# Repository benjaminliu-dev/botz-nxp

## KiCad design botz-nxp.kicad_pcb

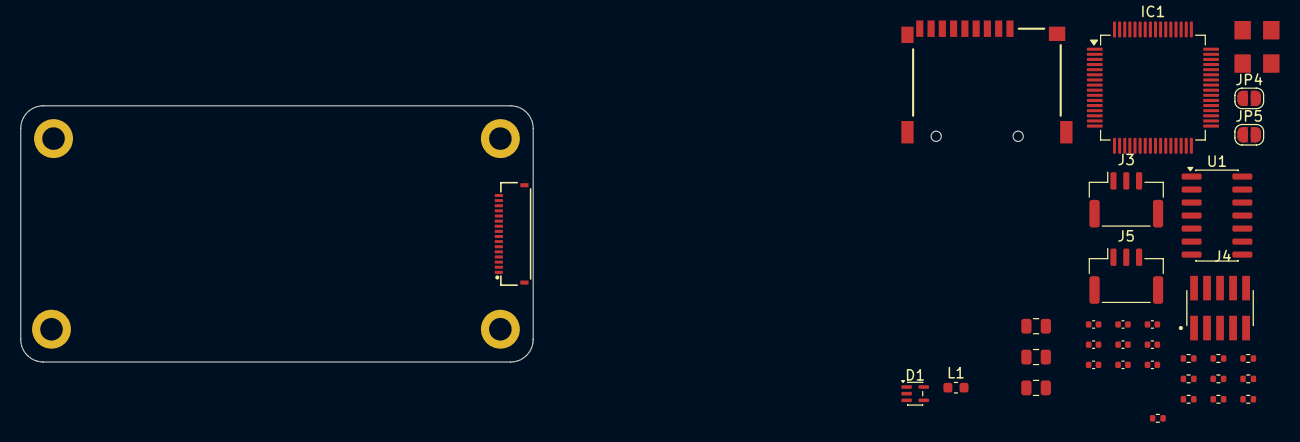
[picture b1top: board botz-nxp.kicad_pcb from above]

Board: 2 copper layers, 50.0 x 25.0 mm, 35 parts (0 on the bottom side), 31 nets, no tracks yet.

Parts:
C1, C2, C3, C4, C8, C9, C13, C15: 0.1uF; C_0402_1005Metric
C5, C6, C14: 10uF; C_0805_2012Metric
C7: 10uF; C_0402_1005Metric
D1: PESD5V0L4UG; SOT-353_SC-70-5
F1: 6V/0.75A/1.5A; 1206
F2: 6V/0.5A/1A; 1206
IC1: MCXA265VLH; LQFP-64_10x10mm_P0.5mm
J1: microSD; microSD_External_Pin
J3, J5: JST_1GH_3; JST_GH_SM03B-GHS-TB_1x03-1MP_P1.25mm_Horizontal
J4: Conn_ARM_JTAG_SWD_10; AMPHENOL_20021121-00010C1LF
J6: Conn_01x16_FPC_0.5mm; FPC_1x16_P0.5mm_Horizontal_DualContact
JP4, JP5: Jumper_2_Open; SolderJumper-2_P1.3mm_Open_RoundedPad1.0x1.5mm
L1: 120 Ohm; L_0603_1608Metric
R1, R3, R4, R5, R6, R7, R8, R10: 10k; R_0402_1005Metric
R2, R9: 120; R_0402_1005Metric
U1: TJA1448AT/0Z; SOIC-14_3.9x8.7mm_P1.27mm

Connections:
3.3V: C1.1, C2.1, C3.1, C4.1, C5.1, C9.2, C14.1, C15.1, D1.3 (K2), F2.2, IC1.13 (VDD_1), IC1.29 (VDD_2), IC1.48 (VDD_3), IC1.60 (VDD_4), J1.4 (VDD), J4.1 (VTref), L1.1, R1.2, R3.2, R4.2, R5.2, R6.2, R7.2, R8.2, U1.11 (VIO)
5V: C7.1, D1.1 (K1), F1.1, U1.3 (VCC)
/3.3V_IN: F2.1, J6.3
/5V_IN: F1.2, J6.1
/BOOT: IC1.53 (P0_6), J6.13, R3.1
/CAN0_H: J3.1, J6.6, R2.2, U1.13 (CANH1)
/CAN0_L: J3.2, J6.7, JP4.1 (A), U1.12 (CANL1)
/CAN0_RX: IC1.59 (P1_3), U1.4 (RXD1)
/CAN0_TX: IC1.58 (P1_2), U1.1 (TXD1)
/CAN1_H: J5.1, J6.10, R9.2, U1.10 (CANH2)
/CAN1_L: J5.2, J6.11, JP5.1 (A), U1.9 (CANL2)
/CAN1_RX: IC1.56 (P1_0), U1.7 (RXD2)
/CAN1_TX: IC1.57 (P1_1), U1.6 (TXD2)
/J_RX: D1.5 (K4), IC1.3 (P1_9), J6.5
/J_TX: D1.4 (K3), IC1.2 (P1_8), J6.4
/NRST: C13.2, IC1.8 (P1_29), J4.10 (~RESET), J6.14, R1.1
/SD_CS: IC1.39 (P3_11), J1.2 (DAT3/CD), R4.1
/SD_DAT1: J1.8 (DAT1), R6.1
/SD_DAT2: J1.1 (DAT2), R7.1
/SD_DET: IC1.16 (P2_2), J1.9 (~DET), R8.1
/SD_MISO: IC1.41 (P3_9), J1.7 (DAT0/SDO), R5.1
/SD_MOSI: IC1.42 (P3_8), J1.3 (CMD/SDI)
/SD_SCK: IC1.40 (P3_10), J1.5 (CLK/SCK)
/SWCLK: IC1.50 (P0_1), J4.4 (SWCLK/TCK)
/SWDIO: IC1.49 (P0_0), J4.2 (SWDIO/TMS)
/SWO: IC1.51 (P0_2), J4.6 (SWO/TDO)
/VDDA: C6.1, C8.1, IC1.12 (VREFH/VDD_ANA), L1.2
GND: C1.2, C2.2, C3.2, C4.2, C5.2, C6.2, C7.2, C8.2, C9.1, C13.1, C14.2, C15.2, D1.2 (A), IC1.11 (VSS/VREFL), IC1.28 (VSS_1), IC1.47 (VSS_2), IC1.61 (VSS_3), J1.6 (VSS), J1.10 (SHIELD), J3.3, J4.3 (GND), J4.5 (GND), J4.9 (GNDDetect), J5.3, J6.2, J6.8, J6.9, J6.12, R10.1, U1.2 (GND), U1.5 (GND), U1.8 (STB2), U1.14 (STB1)
unnamed: IC1.25 (VDD_USB), R10.2
unnamed: JP4.2 (B), R2.1
unnamed: JP5.2 (B), R9.1

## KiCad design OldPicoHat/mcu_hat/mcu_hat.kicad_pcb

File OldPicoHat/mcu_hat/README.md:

Raspberry Pi Pico HAT, made by Arnav G

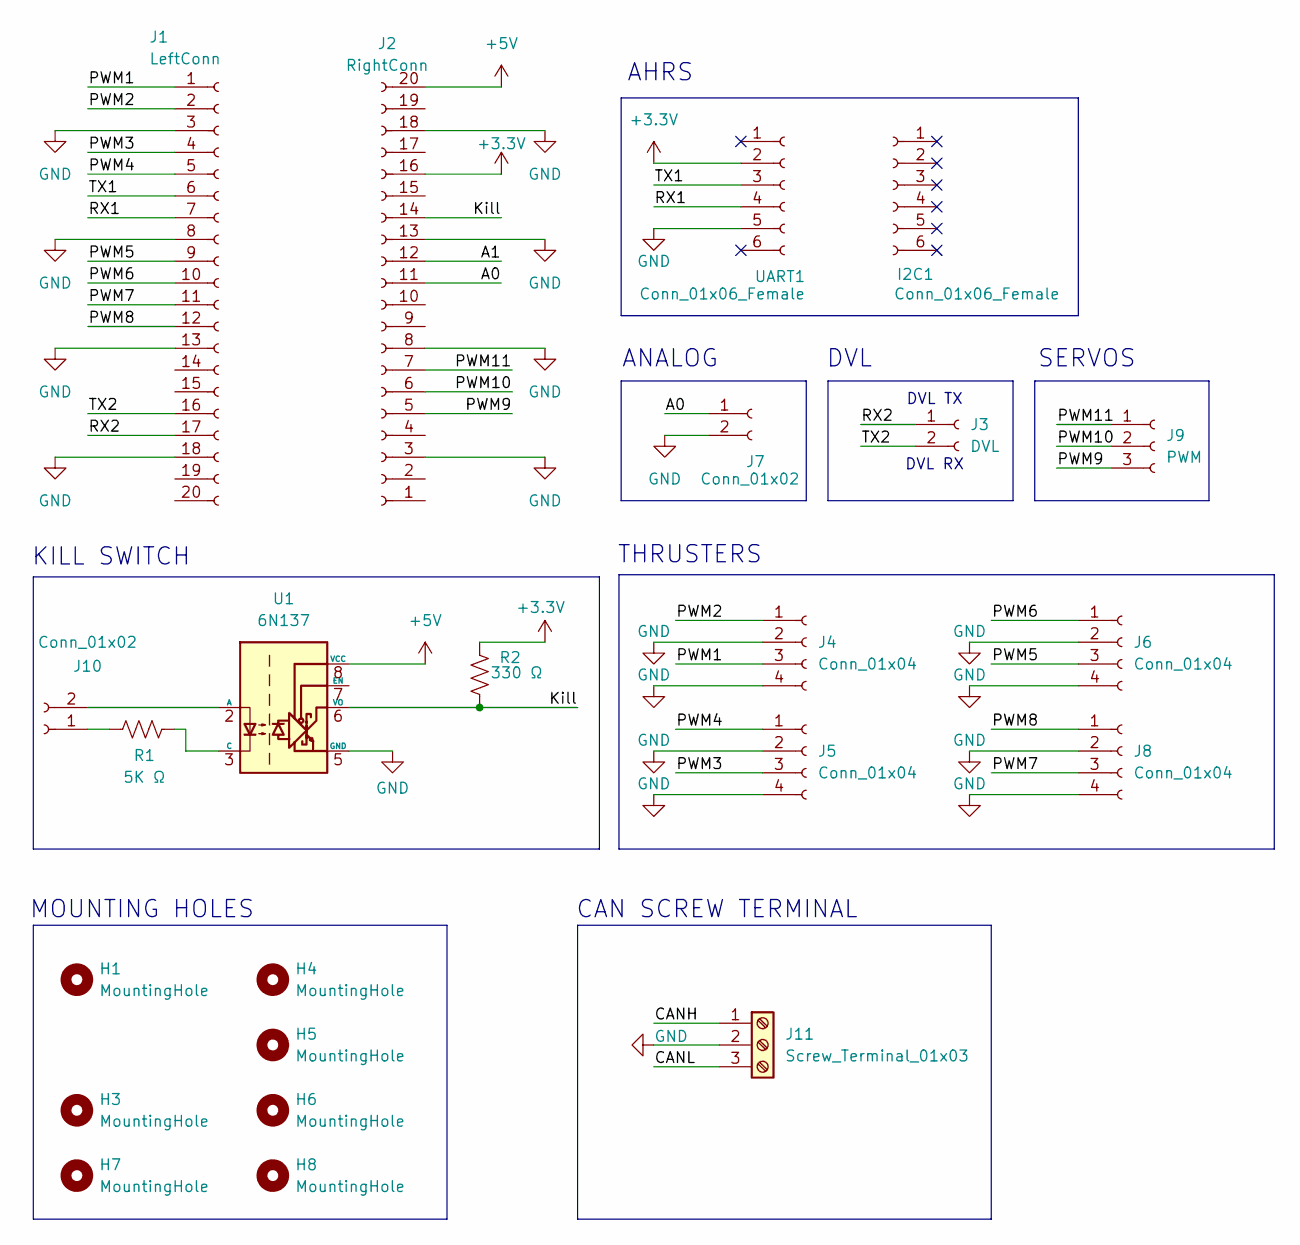
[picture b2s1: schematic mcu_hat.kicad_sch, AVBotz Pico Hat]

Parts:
H1, H3, H4, H5, H6, H7, H8: MountingHole; MountingHole_2.1mm
I2C1: Conn_01x06_Female; PinSocket_1x06_P2.54mm_Vertical
J1: LeftConn; PinSocket_1x20_P2.54mm_Vertical
J2: RightConn; PinSocket_1x20_P2.54mm_Vertical
J3: DVL; Molex_KK-396_A-41792-0002_1x02_P3.96mm_Horizontal
J4, J5, J6, J8: Conn_01x04; Molex_KK-396_A-41792-0004_1x04_P3.96mm_Horizontal
J7, J10: Conn_01x02; Molex_KK-396_A-41792-0002_1x02_P3.96mm_Horizontal
J9: PWM; Molex_KK-396_A-41792-0003_1x03_P3.96mm_Horizontal
J11: Screw_Terminal_01x03; TerminalBlock_Phoenix_PT-1,5-3-3.5-H_1x03_P3.50mm_Horizontal
R1: 5K Ω; R_Axial_DIN0207_L6.3mm_D2.5mm_P10.16mm_Horizontal
R2: 330 Ω; R_Axial_DIN0207_L6.3mm_D2.5mm_P10.16mm_Horizontal
U1: 6N137; DIP-8_W7.62mm
UART1: Conn_01x06_Female; PinSocket_1x06_P2.54mm_Vertical

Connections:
+3.3V: J2.16, R2.2, UART1.2
+5V: J2.20, U1.8 (VCC)
/A0: J2.11, J7.1
/A1: J2.12
/Kill: J2.14, R2.1, U1.6 (VO)
/PWM1: J1.1, J4.3
/PWM2: J1.2, J4.1
/PWM3: J1.4, J5.3
/PWM4: J1.5, J5.1
/PWM5: J1.9, J6.3
/PWM6: J1.10, J6.1
/PWM7: J1.11, J8.3
/PWM8: J1.12, J8.1
/PWM9: J2.5, J9.3
/PWM10: J2.6, J9.2
/PWM11: J2.7, J9.1
/RX1: J1.7, UART1.4
/RX2: J1.17, J3.1
/TX1: J1.6, UART1.3
/TX2: J1.16, J3.2
GND: J1.3, J1.8, J1.13, J1.18, J2.3, J2.8, J2.13, J2.18, J4.2, J4.4, J5.2, J5.4, J6.2, J6.4, J7.2, J8.2, J8.4, J11.2, U1.5 (GND), UART1.5
unnamed: J10.1, R1.1
unnamed: J10.2, U1.2 (A)
unnamed: R1.2, U1.3 (C)

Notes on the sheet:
DVL TX
THRUSTERS
DVL RX
SERVOS
ANALOG
KILL SWITCH
CAN SCREW TERMINAL
DVL
AHRS
MOUNTING HOLES

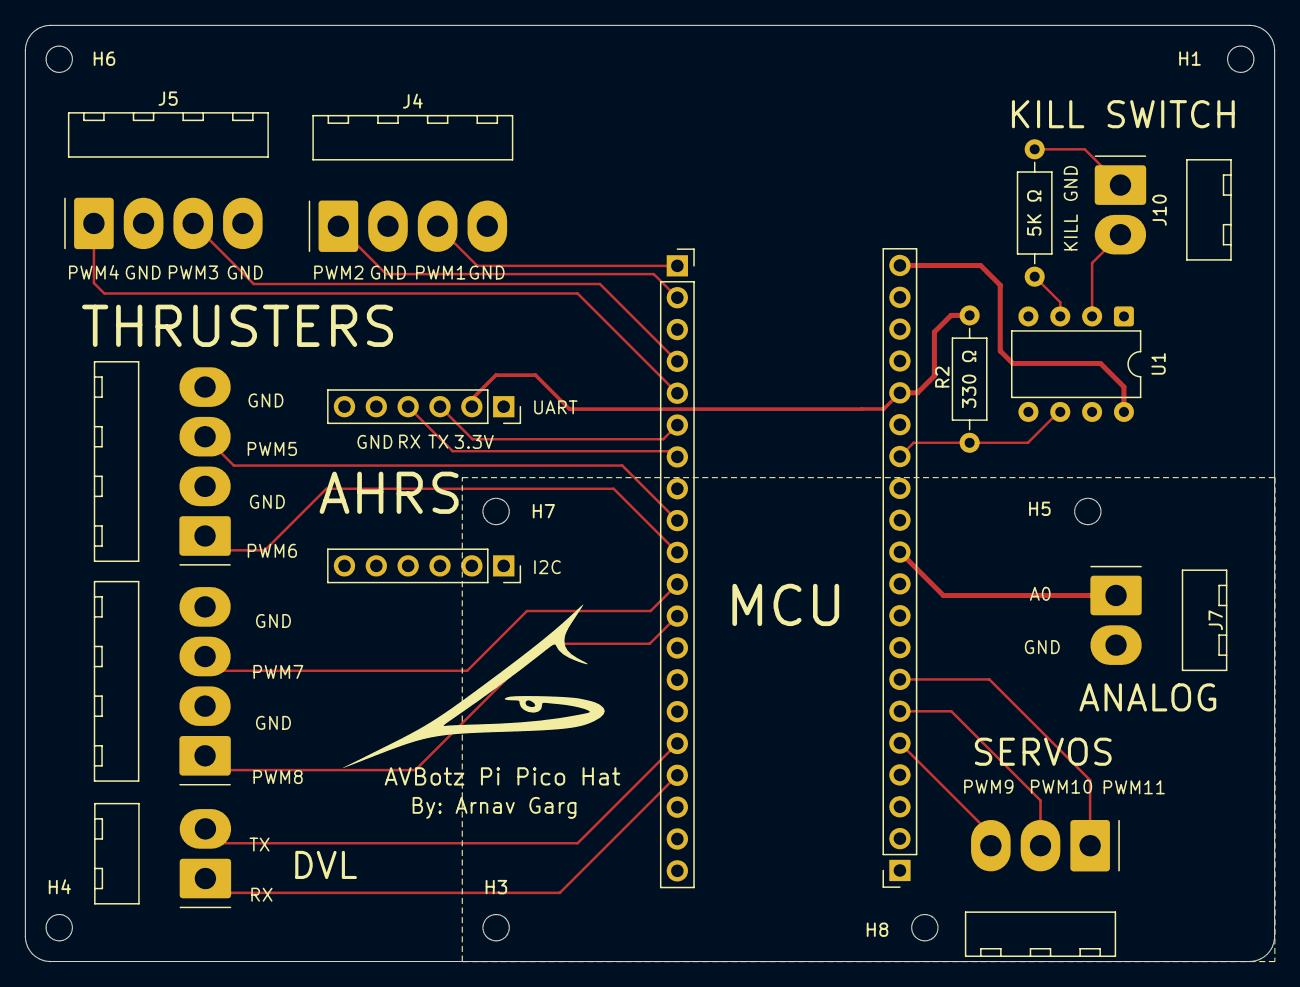
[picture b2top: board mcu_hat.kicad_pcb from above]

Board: 2 copper layers, 99.7 x 74.7 mm, 22 parts (0 on the bottom side), 23 nets.
